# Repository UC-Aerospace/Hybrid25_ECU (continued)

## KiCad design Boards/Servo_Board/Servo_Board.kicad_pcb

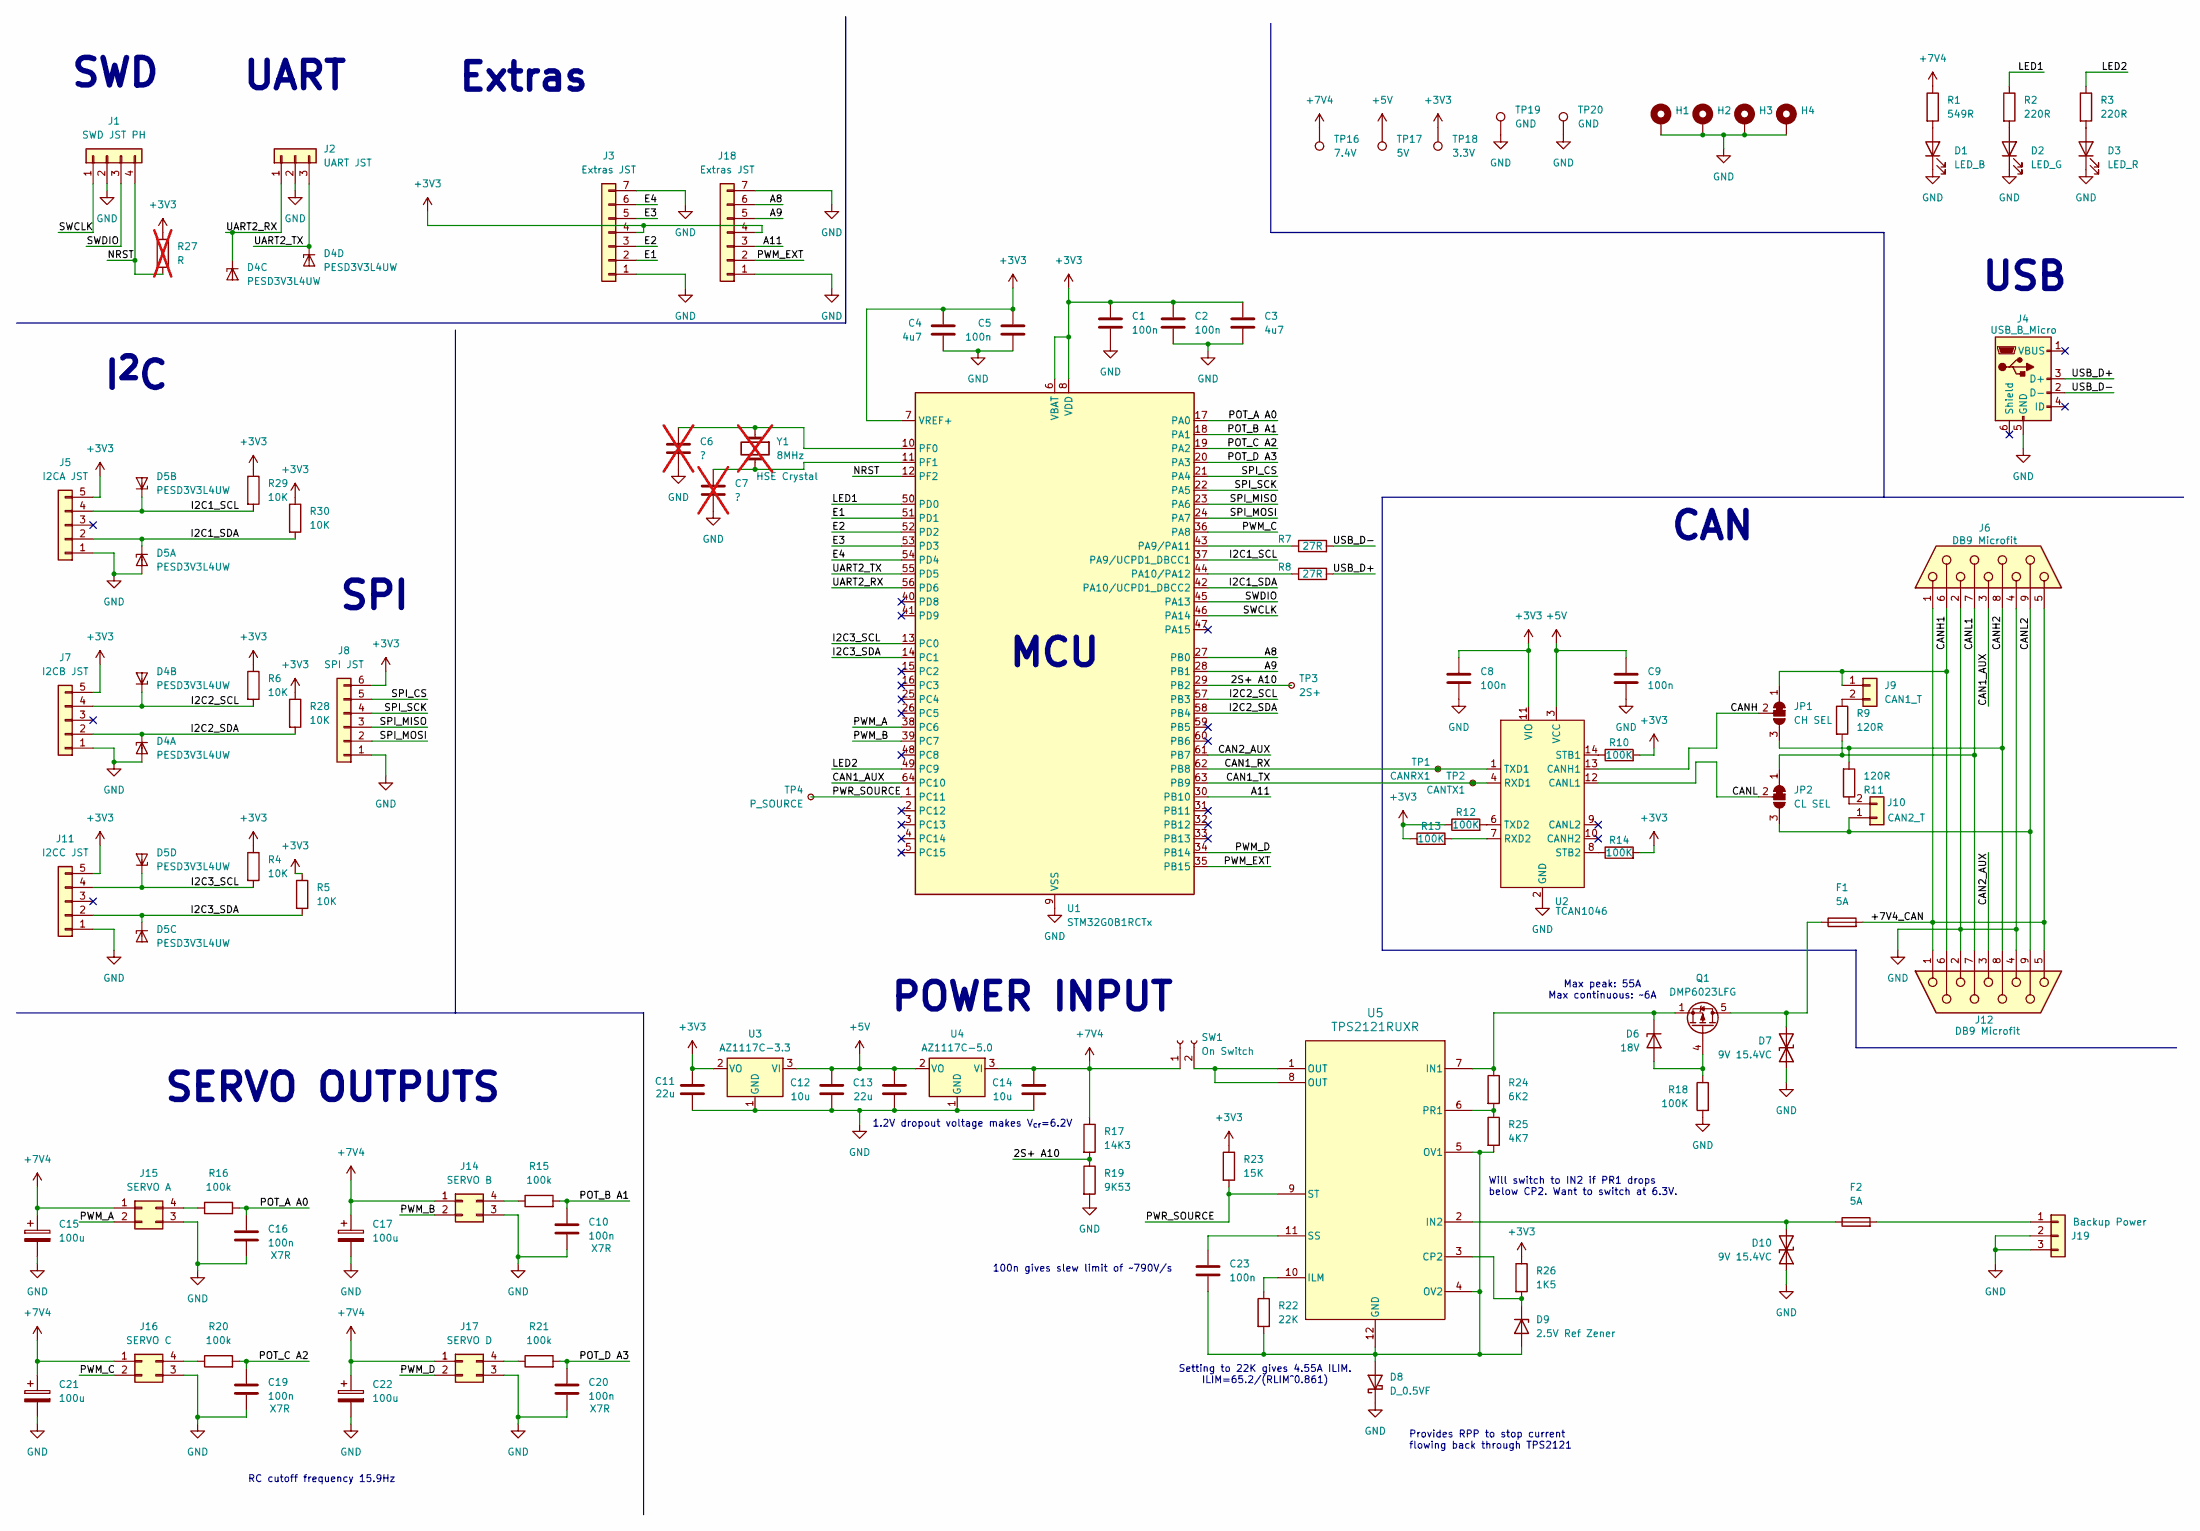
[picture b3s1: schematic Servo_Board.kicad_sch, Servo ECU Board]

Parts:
C1, C2, C5: 100n; C_0402_1005Metric
C3, C4: 4u7; C_0603_1608Metric
C6, C7: ?; C_0402_1005Metric; not fitted
C8, C9, C10, C16, C19, C20, C23: 100n; C_0603_1608Metric
C11, C13: 22u; C_1206_3216Metric
C12, C14: 10u; C_0603_1608Metric
C15, C17, C21, C22: 100u; CP_Elec_6.3x5.9; MPN SVZ1CM101E06E00RAXXX
D1: LED_B; LED_1206_3216Metric; MPN LTST-C150KRKT
D2: LED_G; LED_1206_3216Metric; MPN LTST-C150KGKT
D3: LED_R; LED_1206_3216Metric; MPN LTST-C150TBKT
D4, D5: PESD3V3L4UW; SOT-665
D6: 18V; D_SOD-323F; MPN MM3Z18VB
D7, D10: 9V 15.4VC; D_SOD-123F; MPN SMF9.0CA
D8: D_0.5VF; D_SOD-523; MPN RB521S30T5G
D9: 2.5V Ref Zener; SOT-23-3; MPN LM4040CYM3-2.5-TR
F1, F2: 5A; Fuse_1206_3216Metric
H1, H2, H3, H4: MountingHole_3.2mm_M3_DIN965_Pad_TopOnly
J1: SWD JST PH; JST_PH_B4B-PH-K_1x04_P2.00mm_Vertical; MPN B4B-PH-K-S
J2: UART JST; JST_PH_B3B-PH-K_1x03_P2.00mm_Vertical; MPN B3B-PH-K-S
J3, J18: Extras JST; JST_PH_B7B-PH-K_1x07_P2.00mm_Vertical; MPN B7B-PH-K-S
J4: USB_B_Micro; USB_Micro-B_Amphenol_10118193-0001LF_Horizontal; MPN 10118193-0001LF
J5: I2CA JST; JST_PH_B5B-PH-K_1x05_P2.00mm_Vertical; MPN B6B-PH-K-S
J6, J12: DB9 Microfit; DSUB-9_Pins_Horizontal_P2.77x2.84mm_EdgePinOffset7.70mm_Hou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; MPN 0430451027
J7: I2CB JST; JST_PH_B5B-PH-K_1x05_P2.00mm_Vertical; MPN B5B-PH-K-S
J8: SPI JST; JST_PH_B6B-PH-K_1x06_P2.00mm_Vertical
J9: CAN1_T; PinHeader_1x02_P2.54mm_Vertical
J10: CAN2_T; PinHeader_1x02_P2.54mm_Vertical
J11: I2CC JST; JST_PH_B5B-PH-K_1x05_P2.00mm_Vertical; MPN B5B-PH-K-S
J14: SERVO B; Molex_Micro-Fit_3.0_43045-0412_2x02_P3.00mm_Vertical; MPN 0430450412
J15: SERVO A; Molex_Micro-Fit_3.0_43045-0412_2x02_P3.00mm_Vertical; MPN 0430450412
J16: SERVO C; Molex_Micro-Fit_3.0_43045-0412_2x02_P3.00mm_Vertical; MPN 0430450412
J17: SERVO D; Molex_Micro-Fit_3.0_43045-0412_2x02_P3.00mm_Vertical; MPN 0430450412
J19: Backup Power; Molex_Micro-Fit_3.0_43650-0315_1x03_P3.00mm_Vertical; MPN 436500315
JP1: CH SEL; SolderJumper-3_P1.3mm_Bridged12_RoundedPad1.0x1.5mm
JP2: CL SEL; SolderJumper-3_P1.3mm_Bridged12_RoundedPad1.0x1.5mm
Q1: DMP6023LFG; Diodes_PowerDI3333-8; MPN DMP6023LFG-7
R1: 549R; R_0603_1608Metric
R2, R3: 220R; R_0603_1608Metric
R4, R5, R6, R28, R29, R30: 10K; R_0603_1608Metric
R7, R8: 27R; R_0603_1608Metric
R9, R11: 120R; R_0603_1608Metric
R10, R12, R13, R14, R18: 100K; R_0603_1608Metric
R15, R16, R20, R21: 100k; R_0603_1608Metric
R17: 14K3; R_0603_1608Metric
R19: 9K53; R_0603_1608Metric
R22: 22K; R_0603_1608Metric
R23: 15K; R_0603_1608Metric
R24: 6K2; R_0603_1608Metric
R25: 4K7; R_0603_1608Metric
R26: 1K5; R_0603_1608Metric
R27: R; R_0603_1608Metric; not fitted
SW1: On Switch; Molex_Micro-Fit_3.0_43650-0215_1x02_P3.00mm_Vertical; MPN 436500228
TP1: CANRX1; TestPoint_Pad_D1.0mm
TP2: CANTX1; TestPoint_Pad_D1.0mm
TP3: 2S+; TestPoint_Pad_D1.0mm
TP4: P_SOURCE; TestPoint_Pad_D1.0mm
TP16: 7.4V; TestPoint_Pad_D1.0mm
TP17: 5V; TestPoint_Pad_D1.0mm
TP18: 3.3V; TestPoint_Pad_D1.0mm
TP19, TP20: GND; TestPoint_Bridge_Pitch2.54mm_Drill1.3mm
U1: STM32G0B1RCTx; LQFP-64_10x10mm_P0.5mm; MPN STM32G0B1RCT6
U2: TCAN1046; SOT23_DYY_TEX; MPN TCAN1046AVDYYRQ1
U3: AZ1117C-3.3; SOT-223-3_TabPin2; MPN AZ1117CH-3.3TRG1
U4: AZ1117C-5.0; SOT-223-3_TabPin2; MPN AZ1117CH-5.0TRG1
U5: TPS2121RUXR; RUX0012A; MPN TPS2121RUXR
Y1: 8MHz; Crystal_SMD_Abracon_ABM8G-4Pin_3.2x2.5mm; not fitted

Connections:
+3V3: C1.1, C2.1, C3.1, C4.1, C5.1, C8.1, C11.1, J3.4, J5.5, J7.5, J8.6, J11.5, J18.4, R4.1, R5.1, R6.1, R10.2, R12.1, R13.1, R14.2, R23.1, R26.1, R27.2, R28.1, R29.1, R30.1, TP18.1, U1.6 (VBAT), U1.7 (VREF+), U1.8 (VDD), U2.11 (VIO), U3.2 (VO)
+5V: C9.1, C12.1, C13.1, TP17.1, U2.3 (VCC), U3.3 (VI), U4.2 (VO)
+7V4: C14.1, C15.1, C17.1, C21.1, C22.1, J14.1, J15.1, J16.1, J17.1, R1.1, R17.1, SW1.1, TP16.1, U4.3 (VI)
/2S+ A10: R17.2, R19.1, TP3.1, U1.29 (PB2)
/+7V4_CAN: F1.2, J6.1, J6.5, J12.1, J12.5
/A8: J18.6, U1.27 (PB0)
/A9: J18.5, U1.28 (PB1)
/A11: J18.3, U1.30 (PB10)
/CAN1_AUX: J6.3, U1.64 (PC10)
/CAN1_RX: TP1.1, U1.62 (PB8), U2.1 (TXD1)
/CAN1_TX: TP2.1, U1.63 (PB9), U2.4 (RXD1)
/CAN2_AUX: J12.3, U1.61 (PB7)
/CANH: JP1.2 (C), U2.13 (CANH1)
/CANH1: J6.6, J9.1, J12.6, JP1.1 (A)
/CANH2: J6.8, J12.8, JP1.3 (B), R11.2
/CANL: JP2.2 (C), U2.12 (CANL1)
/CANL1: J6.7, J12.7, JP2.1 (A), R9.2
/CANL2: J6.9, J10.1, J12.9, JP2.3 (B)
/E1: J3.2, U1.51 (PD1)
/E2: J3.3, U1.52 (PD2)
/E3: J3.5, U1.53 (PD3)
/E4: J3.6, U1.54 (PD4)
/I2C1_SCL: D5.3 (K2), J5.4, R29.2, U1.37 (PA9/UCPD1_DBCC1)
/I2C1_SDA: D5.1 (K1), J5.2, R30.2, U1.42 (PA10/UCPD1_DBCC2)
/I2C2_SCL: D4.3 (K2), J7.4, R6.2, U1.57 (PB3)
/I2C2_SDA: D4.1 (K1), J7.2, R28.2, U1.58 (PB4)
/I2C3_SCL: D5.5 (K4), J11.4, R4.2, U1.13 (PC0)
/I2C3_SDA: D5.4 (K3), J11.2, R5.2, U1.14 (PC1)
/LED1: R2.1, U1.50 (PD0)
/LED2: R3.1, U1.49 (PC9)
/NRST: J1.4, R27.1, U1.12 (PF2)
/POT_A A0: C16.1, R16.2, U1.17 (PA0)
/POT_B A1: C10.1, R15.2, U1.18 (PA1)
/POT_C A2: C19.1, R20.2, U1.19 (PA2)
/POT_D A3: C20.1, R21.2, U1.20 (PA3)
/PWM_A: J15.2, U1.38 (PC6)
/PWM_B: J14.2, U1.39 (PC7)
/PWM_C: J16.2, U1.36 (PA8)
/PWM_D: J17.2, U1.34 (PB14)
/PWM_EXT: J18.2, U1.35 (PB15)
/PWR_SOURCE: R23.2, TP4.1, U1.1 (PC11), U5.9 (ST)
/SPI_CS: J8.5, U1.21 (PA4)
/SPI_MISO: J8.3, U1.23 (PA6)
/SPI_MOSI: J8.2, U1.24 (PA7)
/SPI_SCK: J8.4, U1.22 (PA5)
/SWCLK: J1.1, U1.46 (PA14)
/SWDIO: J1.3, U1.45 (PA13)
/UART2_RX: D4.4 (K3), J2.1, U1.56 (PD6)
/UART2_TX: D4.5 (K4), J2.3, U1.55 (PD5)
/USB_D+: J4.3 (D+), R8.2
/USB_D-: J4.2 (D-), R7.2
GND: C1.2, C2.2, C3.2, C4.2, C5.2, C6.2, C7.2, C8.2, C9.2, C10.2, C11.2, C12.2, C13.2, C14.2, C15.2, C16.2, C17.2, C19.2, C20.2, C21.2, C22.2, D1.1 (K), D2.1 (K), D3.1 (K), D4.2 (A), D5.2 (A), D7.1 (A1), D8.1 (K), D10.1 (A1), H1.1, H2.1, H3.1, H4.1, J1.2, J2.2, J3.1, J3.7, J4.5 (GND), J5.1, J6.2, J6.4, J7.1, J8.1, J11.1, J12.2, J12.4, J14.3, J15.3, J16.3, J17.3, J18.1, J18.7, J19.2, J19.3, R18.2, R19.2, TP19.1, TP20.1, U1.9 (VSS), U2.2 (GND), U2.5 (GND), U3.1 (GND), U4.1 (GND)
unnamed: D1.2 (A), R1.2
unnamed: D2.2 (A), R2.2
unnamed: D3.2 (A), R3.2
unnamed: D6.2 (A), Q1.4 (G), R18.1
unnamed: D6.1 (K), Q1.1 (S), Q1.2 (S), Q1.3 (S), R24.1, U5.7 (IN1)
unnamed: D7.2 (A2), F1.1, Q1.5 (D)
unnamed: C23.2, D8.2 (A), D9.2 (A), R22.2, R25.2, U5.4 (OV2), U5.5 (OV1), U5.12 (GND)
unnamed: D9.1 (K), R26.2, U5.3 (CP2)
unnamed: D10.2 (A2), F2.1, U5.2 (IN2)
unnamed: J9.2, R9.1
unnamed: J10.2, R11.1
unnamed: J14.4, R15.1
unnamed: J15.4, R16.1
unnamed: J16.4, R20.1
unnamed: J17.4, R21.1
unnamed: F2.2, J19.1
unnamed: SW1.2, U5.1 (OUT), U5.8 (OUT)
unnamed: R7.1, U1.43 (PA9/PA11)
unnamed: R8.1, U1.44 (PA10/PA12)
unnamed: C6.1, U1.10 (PF0), Y1.1
unnamed: C7.1, U1.11 (PF1), Y1.3 (2)
unnamed: R13.2, U2.7 (RXD2)
unnamed: R10.1, U2.14 (STB1)
unnamed: R14.1, U2.8 (STB2)
unnamed: R12.2, U2.6 (TXD2)
unnamed: R22.1, U5.10 (ILM)
unnamed: R24.2, R25.1, U5.6 (PR1)
unnamed: C23.1, U5.11 (SS)

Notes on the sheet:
Extras
Max peak: 55A Max continuous: ~6A
SPI
MCU
CAN
Will switch to IN2 if PR1 drops below CP2. Want to switch at 6.3V.
RC cutoff frequency 15.9Hz
POWER INPUT
UART
I^{2}C
SERVO OUTPUTS
100n gives slew limit of ~790V/s
Setting to 22K gives 4.55A ILIM. ILIM=65.2/(RLIM^0.861)
1.2V dropout voltage makes V_{cr}=6.2V
USB
Provides RPP to stop current flowing back through TPS2121
SWD

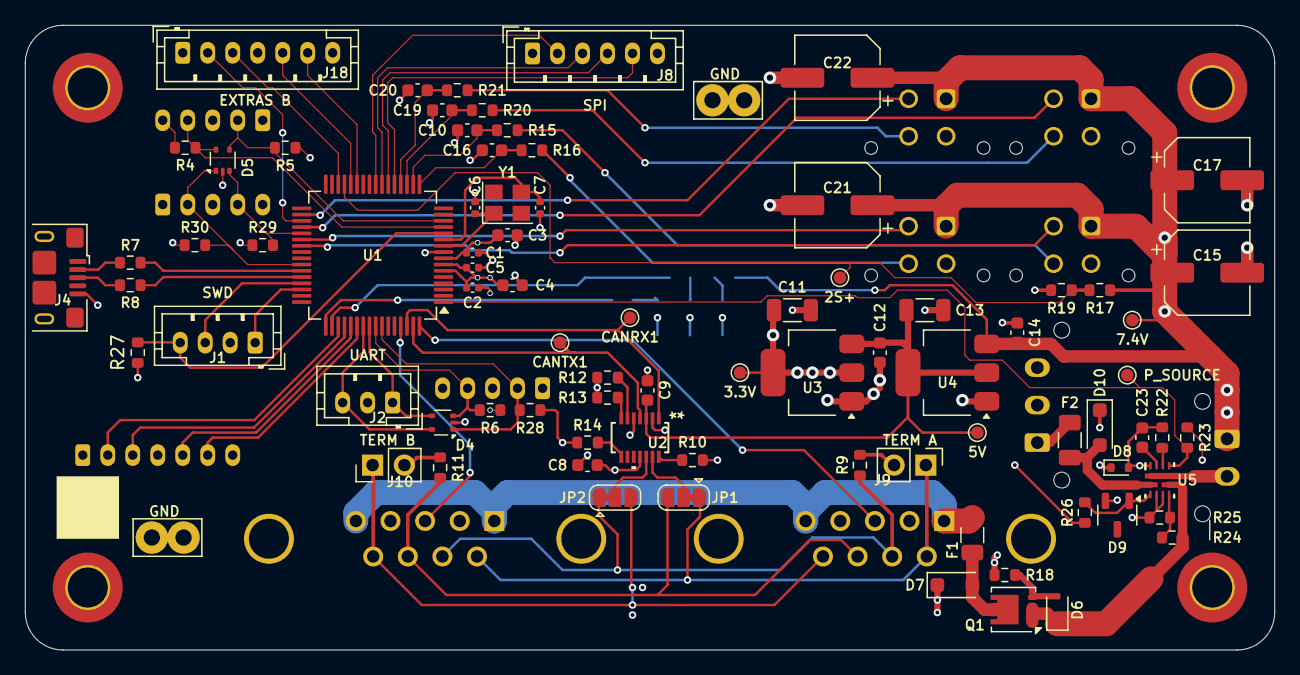
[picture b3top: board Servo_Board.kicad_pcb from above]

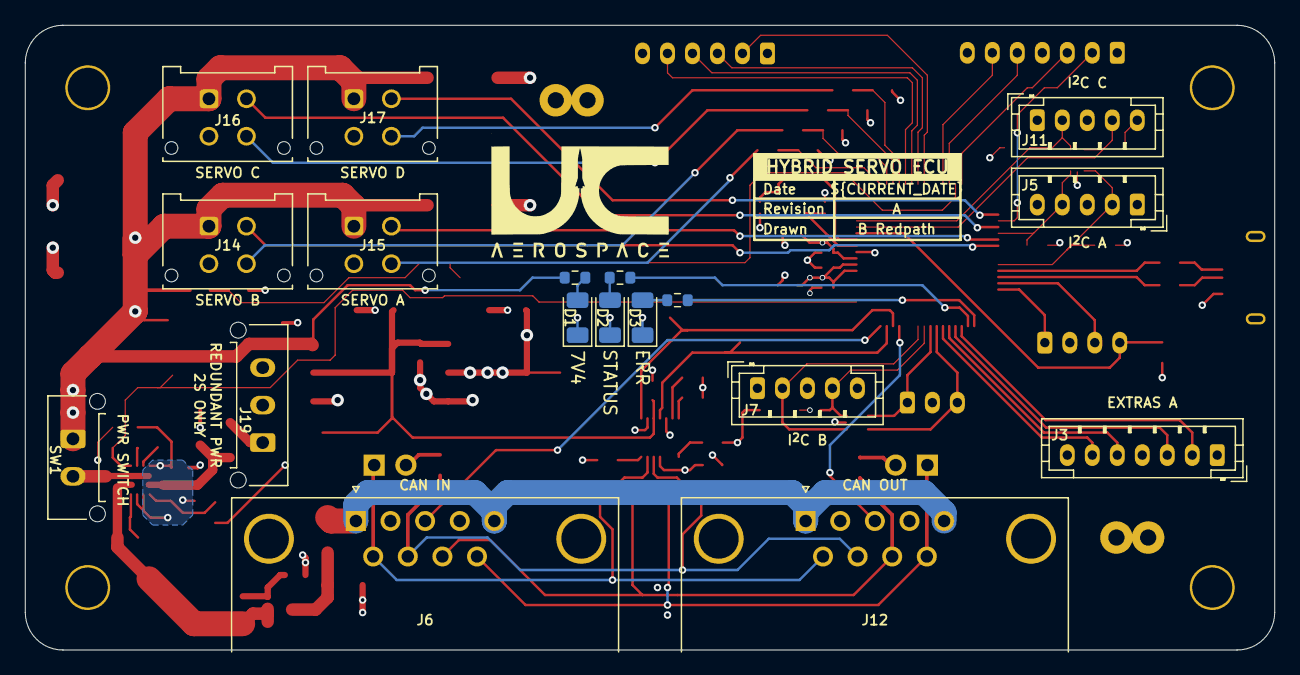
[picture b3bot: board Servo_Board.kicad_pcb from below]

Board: 4 copper layers, 100.0 x 50.0 mm, 105 parts (18 on the bottom side), 80 nets.

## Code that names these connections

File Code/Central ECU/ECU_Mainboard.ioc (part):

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Mcu.Name=STM32G0B1R(B-C-E)Tx
Mcu.Package=LQFP64
Mcu.UserName=STM32G0B1RCTx
PA0.Mode=IN0
PA0.Signal=ADC1_IN0
PA1.Mode=IN1
PA1.Signal=ADC1_IN1
PA11\ [PA9].Mode=Device
PA11\ [PA9].Signal=USB_DM
PA12\ [PA10].Mode=Device
PA12\ [PA10].Signal=USB_DP
PA13.Mode=Serial_Wire
PA13.Signal=SYS_SWDIO
PA14-BOOT0.Mode=Serial_Wire
PA14-BOOT0.Signal=SYS_SWCLK
PA2.Mode=IN2
PA2.Signal=ADC1_IN2
PA3.Mode=IN3
PA3.Signal=ADC1_IN3
PA4.GPIOParameters=GPIO_Speed,PinState,GPIO_Label
PA4.GPIO_Label=SPI1_CSS
PA4.GPIO_Speed=GPIO_SPEED_FREQ_HIGH
PA4.PinState=GPIO_PIN_SET
PA4.Signal=GPIO_Output
PA5.Mode=Full_Duplex_Master
PA5.Signal=SPI1_SCK
PA6.Mode=Full_Duplex_Master
PA6.Signal=SPI1_MISO
PA7.Mode=Full_Duplex_Master
PA7.Signal=SPI1_MOSI
PB12.GPIOParameters=GPIO_Label
PB12.GPIO_Label=CAN2_AUX
PB12.Signal=GPIO_Input
PB13.GPIOParameters=GPIO_Label
PB13.GPIO_Label=CAN1_AUX
PB13.Signal=GPIO_Input
PB14.GPIOParameters=GPIO_Label
PB14.GPIO_Label=PGOOD_HS
PB14.Signal=GPIO_Input
PB15.GPIOParameters=GPIO_Label
PB15.GPIO_Label=IMON_HS
PB15.Signal=GPIO_Input
PB3.Mode=I2C
PB3.Signal=I2C2_SCL
PB4.Mode=I2C
PB4.Signal=I2C2_SDA
PB6.GPIOParameters=GPIO_Speed
PB6.GPIO_Speed=GPIO_SPEED_FREQ_VERY_HIGH
PB6.Mode=Asynchronous
PB6.Signal=USART1_TX
PB7.GPIOParameters=GPIO_Speed,GPIO_PuPd
PB7.GPIO_PuPd=GPIO_NOPULL
PB7.GPIO_Speed=GPIO_SPEED_FREQ_VERY_HIGH
PB7.Mode=Asynchronous
PB7.Signal=USART1_RX
PB8.Mode=I2C
PB8.Signal=I2C1_SCL
PB9.Mode=I2C
PB9.Signal=I2C1_SDA
PC0.Mode=I2C
PC0.Signal=I2C3_SCL
PC1.Mode=I2C
PC1.Signal=I2C3_SDA
PC10.GPIOParameters=GPIO_Label
PC10.GPIO_Label=OX_FIRE
PC10.Signal=GPIO_Output
PC11.GPIOParameters=GPIO_Label
PC11.GPIO_Label=EMATCH2_FIRE
PC11.Signal=GPIO_Output
PC12.GPIOParameters=GPIO_Label
PC12.GPIO_Label=EMATCH1_FIRE
PC12.Signal=GPIO_Output
PC13.GPIOParameters=GPIO_Label
PC13.GPIO_Label=ARM_HS
PC13.Signal=GPIO_Output
PC14-OSC32_IN\ (PC14).Mode=LSE-External-Oscillator
PC14-OSC32_IN\ (PC14).Signal=RCC_OSC32_IN
PC15-OSC32_OUT\ (PC15).Mode=LSE-External-Oscillator
PC15-OSC32_OUT\ (PC15).Signal=RCC_OSC32_OUT
PC4.Mode=FDCAN_Activate
PC4.Signal=FDCAN1_RX
PC5.Mode=FDCAN_Activate
PC5.Signal=FDCAN1_TX
PC6.GPIOParameters=GPIO_PuPd,GPIO_Label
PC6.GPIO_Label=EMATCH2_CONT
PC6.GPIO_PuPd=GPIO_PULLUP
PC6.Signal=GPIO_Input
PC7.GPIOParameters=GPIO_PuPd,GPIO_Label
PC7.GPIO_Label=EMATCH1_CONT
PC7.GPIO_PuPd=GPIO_PULLUP
PC7.Signal=GPIO_Input
PC8.GPIOParameters=GPIO_PuPd,GPIO_Label
PC8.GPIO_Label=OX_LOWSIDE_SENSE
PC8.GPIO_PuPd=GPIO_PULLUP
PC8.Signal=GPIO_Input
PC9.GPIOParameters=GPIO_PuPd,GPIO_Label
PC9.GPIO_Label=SENSE_12V
PC9.GPIO_PuPd=GPIO_PULLUP
PC9.Signal=GPIO_Input
PD0.GPIOParameters=GPIO_Label
PD0.GPIO_Label=LED_STATUS
PD0.Signal=GPIO_Output
PD1.GPIOParameters=PinState,GPIO_PuPd,GPIO_Label,GPIO_ModeDefaultOutputPP
PD1.GPIO_Label=LED_IND_GREEN
PD1.GPIO_ModeDefaultOutputPP=GPIO_MODE_OUTPUT_OD
PD1.GPIO_PuPd=GPIO_NOPULL
PD1.PinState=GPIO_PIN_SET
PD1.Signal=GPIO_Output
PD2.GPIOParameters=PinState,GPIO_PuPd,GPIO_Label,GPIO_ModeDefaultOutputPP
PD2.GPIO_Label=LED_IND_ERROR
PD2.GPIO_ModeDefaultOutputPP=GPIO_MODE_OUTPUT_OD
PD2.GPIO_PuPd=GPIO_NOPULL
PD2.PinState=GPIO_PIN_SET
PD2.Signal=GPIO_Output
PD3.GPIOParameters=PinState,GPIO_PuPd,GPIO_Label,GPIO_ModeDefaultOutputPP
PD3.GPIO_Label=IND_HORN
PD3.GPIO_ModeDefaultOutputPP=GPIO_MODE_OUTPUT_OD
PD3.GPIO_PuPd=GPIO_NOPULL
PD3.PinState=GPIO_PIN_SET
PD3.Signal=GPIO_Output
PD4.GPIOParameters=GPIO_Label
PD4.GPIO_Label=E4
PD4.Signal=GPIO_Input
PD5.Mode=Asynchronous
PD5.Signal=USART2_TX
PD6.Mode=Asynchronous
PD6.Signal=USART2_RX
RCC.HSE_VALUE=8000000
RCC.SYSCLKFreq_VALUE=64000000
RCC.SYSCLKSource=RCC_SYSCLKSOURCE_PLLCLK
board=custom

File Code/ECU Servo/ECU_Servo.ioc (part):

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Mcu.Name=STM32G0B1R(B-C-E)Tx
Mcu.Package=LQFP64
Mcu.UserName=STM32G0B1RCTx
PA0.GPIOParameters=GPIO_Label
PA0.GPIO_Label=POT_A
PA0.Mode=IN0
PA0.Signal=ADC1_IN0
PA1.GPIOParameters=GPIO_Label
PA1.GPIO_Label=POT_B
PA1.Mode=IN1
PA1.Signal=ADC1_IN1
PA10.Mode=I2C
PA10.Signal=I2C1_SDA
PA11\ [PA9].Mode=Device
PA11\ [PA9].Signal=USB_DM
PA12\ [PA10].Mode=Device
PA12\ [PA10].Signal=USB_DP
PA13.Mode=Serial_Wire
PA13.Signal=SYS_SWDIO
PA14-BOOT0.Mode=Serial_Wire
PA14-BOOT0.Signal=SYS_SWCLK
PA2.GPIOParameters=GPIO_Label
PA2.GPIO_Label=POT_C
PA2.Mode=IN2
PA2.Signal=ADC1_IN2
PA3.GPIOParameters=GPIO_Label
PA3.GPIO_Label=POT_D
PA3.Mode=IN3
PA3.Signal=ADC1_IN3
PA4.Mode=NSS_Signal_Hard_Output
PA4.Signal=SPI1_NSS
PA5.Mode=Full_Duplex_Master
PA5.Signal=SPI1_SCK
PA6.Mode=Full_Duplex_Master
PA6.Signal=SPI1_MISO
PA7.Mode=Full_Duplex_Master
PA7.Signal=SPI1_MOSI
PA8.GPIOParameters=GPIO_Label
PA8.GPIO_Label=PWM_C
PA8.Signal=S_TIM1_CH1
PA9.Mode=I2C
PA9.Signal=I2C1_SCL
PB14.GPIOParameters=GPIO_Label
PB14.GPIO_Label=PWM_D
PB14.Signal=S_TIM15_CH1
PB2.GPIOParameters=GPIO_Label
PB2.GPIO_Label=ADC_2S
PB2.Mode=IN10
PB2.Signal=ADC1_IN10
PB3.Mode=I2C
PB3.Signal=I2C2_SCL
PB4.Mode=I2C
PB4.Signal=I2C2_SDA
PB7.GPIOParameters=GPIO_Label
PB7.GPIO_Label=CAN2_AUX
PB7.Signal=GPIO_Input
PB8.Mode=FDCAN_Activate
PB8.Signal=FDCAN1_RX
PB9.Mode=FDCAN_Activate
PB9.Signal=FDCAN1_TX
PC0.Mode=I2C
PC0.Signal=I2C3_SCL
PC1.Mode=I2C
PC1.Signal=I2C3_SDA
PC10.GPIOParameters=GPIO_Label
PC10.GPIO_Label=CAN1_AUX
PC10.Signal=GPIO_Input
PC11.GPIOParameters=GPIO_Label
PC11.GPIO_Label=PWR_SOURCE
PC11.Signal=GPIO_Input
PC6.GPIOParameters=GPIO_Label
PC6.GPIO_Label=PWM_A
PC6.Signal=S_TIM3_CH1
PC7.GPIOParameters=GPIO_Label
PC7.GPIO_Label=PWM_B
PC7.Signal=S_TIM3_CH2
PC9.GPIOParameters=GPIO_Label
PC9.GPIO_Label=LED_ERROR
PC9.Signal=GPIO_Output
PD0.GPIOParameters=GPIO_Label
PD0.GPIO_Label=LED_STATUS
PD0.Signal=GPIO_Output
PD1.GPIOParameters=PinState,GPIO_PuPd,GPIO_Label,GPIO_ModeDefaultOutputPP
PD1.GPIO_Label=Servo_A_NRST
PD1.GPIO_ModeDefaultOutputPP=GPIO_MODE_OUTPUT_OD
PD1.GPIO_PuPd=GPIO_NOPULL
PD1.PinState=GPIO_PIN_SET
PD1.Signal=GPIO_Output
PD2.GPIOParameters=PinState,GPIO_PuPd,GPIO_Label,GPIO_ModeDefaultOutputPP
PD2.GPIO_Label=Servo_B_NRST
PD2.GPIO_ModeDefaultOutputPP=GPIO_MODE_OUTPUT_OD
PD2.GPIO_PuPd=GPIO_NOPULL
PD2.PinState=GPIO_PIN_SET
PD2.Signal=GPIO_Output
PD3.GPIOParameters=PinState,GPIO_PuPd,GPIO_Label,GPIO_ModeDefaultOutputPP
PD3.GPIO_Label=Servo_C_NRST
PD3.GPIO_ModeDefaultOutputPP=GPIO_MODE_OUTPUT_OD
PD3.GPIO_PuPd=GPIO_NOPULL
PD3.PinState=GPIO_PIN_SET
PD3.Signal=GPIO_Output
PD4.GPIOParameters=PinState,GPIO_PuPd,GPIO_Label,GPIO_ModeDefaultOutputPP
PD4.GPIO_Label=Servo_D_NRST
PD4.GPIO_ModeDefaultOutputPP=GPIO_MODE_OUTPUT_OD
PD4.GPIO_PuPd=GPIO_NOPULL
PD4.PinState=GPIO_PIN_SET
PD4.Signal=GPIO_Output
PD5.Mode=Asynchronous
PD5.Signal=USART2_TX
PD6.Mode=Asynchronous
PD6.Signal=USART2_RX
PF0-OSC_IN\ (PF0).Mode=HSE-External-Oscillator
PF0-OSC_IN\ (PF0).Signal=RCC_OSC_IN
PF1-OSC_OUT\ (PF1).Mode=HSE-External-Oscillator
PF1-OSC_OUT\ (PF1).Signal=RCC_OSC_OUT
RCC.HSE_VALUE=12000000
RCC.SYSCLKFreq_VALUE=64000000
RCC.SYSCLKSource=RCC_SYSCLKSOURCE_PLLCLK
board=custom

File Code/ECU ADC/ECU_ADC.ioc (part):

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Mcu.Name=STM32G0B1R(B-C-E)Tx
Mcu.Package=LQFP64
Mcu.UserName=STM32G0B1RCTx
PA0.GPIOParameters=GPIO_Label
PA0.GPIO_Label=CJT_A0
PA0.Mode=IN0
PA0.Signal=ADC1_IN0
PA1.GPIOParameters=GPIO_Label
PA1.GPIO_Label=MIPAA_A1
PA1.Mode=IN1
PA1.Signal=ADC1_IN1
PA10.Mode=I2C
PA10.Signal=I2C1_SDA
PA11\ [PA9].Mode=Device
PA11\ [PA9].Signal=USB_DM
PA12\ [PA10].Mode=Device
PA12\ [PA10].Signal=USB_DP
PA13.Mode=Serial_Wire
PA13.Signal=SYS_SWDIO
PA14-BOOT0.Mode=Serial_Wire
PA14-BOOT0.Signal=SYS_SWCLK
PA2.GPIOParameters=GPIO_Label
PA2.GPIO_Label=MIPAB_A2
PA2.Mode=IN2
PA2.Signal=ADC1_IN2
PA4.GPIOParameters=PinState,GPIO_Label
PA4.GPIO_Label=SPI_CS
PA4.PinState=GPIO_PIN_SET
PA4.Signal=GPIO_Output
PA5.Mode=Full_Duplex_Master
PA5.Signal=SPI1_SCK
PA6.Mode=Full_Duplex_Master
PA6.Signal=SPI1_MISO
PA7.Mode=Full_Duplex_Master
PA7.Signal=SPI1_MOSI
PA9.Mode=I2C
PA9.Signal=I2C1_SCL
PB0.GPIOParameters=PinState,GPIO_Label
PB0.GPIO_Label=ADC_RST
PB0.PinState=GPIO_PIN_SET
PB0.Signal=GPIO_Output
PB1.GPIOParameters=GPIO_Label
PB1.GPIO_Label=REF5V_B1
PB1.Mode=IN9
PB1.Signal=ADC1_IN9
PB2.GPIOParameters=GPIO_Label
PB2.GPIO_Label=V2S_A10
PB2.Mode=IN10
PB2.Signal=ADC1_IN10
PB3.Mode=I2C
PB3.Signal=I2C2_SCL
PB4.Mode=I2C
PB4.Signal=I2C2_SDA
PB8.Mode=FDCAN_Activate
PB8.Signal=FDCAN1_RX
PB9.Mode=FDCAN_Activate
PB9.Signal=FDCAN1_TX
PC0.Mode=I2C
PC0.Signal=I2C3_SCL
PC1.Mode=I2C
PC1.Signal=I2C3_SDA
PC10.GPIOParameters=GPIO_Label
PC10.GPIO_Label=CAN1_AUX
PC10.Signal=GPIO_Input
PC4.GPIOParameters=GPIO_Label
PC4.GPIO_Label=SYNC
PC4.Signal=GPIO_Output
PC5.GPIOParameters=GPIO_Label
PC5.GPIO_Label=ADC_RDY
PC5.Signal=GPIO_Input
PC9.GPIOParameters=GPIO_Label
PC9.GPIO_Label=LED_IND_ERROR
PC9.Signal=GPIO_Output
PD0.GPIOParameters=GPIO_Label
PD0.GPIO_Label=LED_IND_STATUS
PD0.Signal=GPIO_Output
PD1.GPIOParameters=GPIO_Label
PD1.GPIO_Label=E1
PD1.Signal=GPIO_Input
PD2.GPIOParameters=GPIO_Label
PD2.GPIO_Label=E2
PD2.Signal=GPIO_Input
PD3.GPIOParameters=GPIO_Label
PD3.GPIO_Label=E3
PD3.Signal=GPIO_Input
PD4.GPIOParameters=GPIO_Label
PD4.GPIO_Label=E4
PD4.Signal=GPIO_Input
PD5.Mode=Asynchronous
PD5.Signal=USART2_TX
PD6.Mode=Asynchronous
PD6.Signal=USART2_RX
PF0-OSC_IN\ (PF0).Mode=HSE-External-Oscillator
PF0-OSC_IN\ (PF0).Signal=RCC_OSC_IN
PF1-OSC_OUT\ (PF1).Mode=HSE-External-Oscillator
PF1-OSC_OUT\ (PF1).Signal=RCC_OSC_OUT
RCC.HSE_VALUE=12000000
RCC.SYSCLKFreq_VALUE=64000000
RCC.SYSCLKSource=RCC_SYSCLKSOURCE_PLLCLK
board=custom

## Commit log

2025-03-21 Initial Boilerplate
2025-03-21 Added git ignore and removed backups
2025-03-21 MCU + CAN
2025-03-22 Added 422 and crystal
2025-03-23 Power regulation and crystal for MCU added to servo board.
2025-03-27 More to the central mcu plus started on ignitors and valve control
2025-03-27 CAN transceiver and D-sub connector
2025-03-28 Some more minor tweaks
2025-03-30 Servo board changes:
    Replaced buck converter with LDO voltage regulator.
    Found PWM pins on u-controller and connected them to connectors with flyback diodes.
2025-03-30 D-sub output connector added to servo board
2025-03-31 Added USB and serial programmer to Servo Board. Added servo feedback lines
2025-03-31 Forgot termination resistors
2025-04-01 Added most connectors and hooking up
2025-04-01 Nearing completion
2025-04-02 For review
2025-04-02 Finished Servo board and ADC board for review tomorrow
2025-04-04 Footprints for the servo and ADC board
2025-04-06 Changed to 0603 passives and added NRST line
2025-04-12 Added environmental P+T sensor
2025-04-12 Started layout
2025-04-13 More progress on layout
2025-04-13 Finished central ECU for review
2025-04-13 Tidy up, will send to Chris
2025-04-13 Added PDF of schematic
2025-04-15 Fixed voltage divider and comparator bias
    Re feedback from Chris still need to fix regulator power dissipation. Happy with other points being non-issues at current.
2025-04-17 Central ECU to order
2025-04-17 Rendered and updated pdf plot
2025-05-05 Ongoing changes to satellite boards and test code
2025-05-07 Working test project with CDC enabled.
2025-05-12 Somewhat done servo+adc boards
2025-05-12 Fixes and footprints
    Just thermocouples todo
2025-05-12 Selected thermocouple connector, added ferrite bead
2025-05-12 Added switch to servo board
2025-05-13 Servo nearing completion and ADC 50% layed out
2025-05-14 Nearing complete layout on both boards
2025-05-15 Completed with manufacturing files
2025-06-06 Cleaning out code for firmware
2025-06-06 Prep for ADC+Servo
2025-06-06 Some intital print functions and setting up for UID locking
2025-06-10 Updated resistors on ECU, added code to read battery voltages
2025-06-10 Added some basic OLED code to test
2025-06-12 OLED working and displaying battery percentage
2025-06-12 Minor change to CAN rates
2025-06-12 AI Spaghetti!
2025-06-13 Turns out SD is problematic
2025-06-15 RTC + SD card working
2025-06-20 RS422 still an issue
2025-07-15 Start code for servo, USB not working
2025-07-15 Rev B ADC Board
    Change ADC to QFN due to order error
    Adds voltage divider to MIPA ADC lines
2025-07-19 Added servo boiler code
2025-07-19 Unsure of change
2025-07-19 Ongoing
2025-07-21 More ongoing work, fleshed out protocol
2025-07-21 Forgot to commit ioc
2025-07-21 Updates to board to refelct rework state
2025-07-22 SD benchmarking
2025-07-22 Copilot slop
2025-07-22 Bunch of fanagling to get working and speed up SD card
2025-07-22 Removed test code
2025-07-28 CAN mainly working
2025-07-28 Some PCB changes after ADC assembly
2025-07-28 Changes before branching to make servos work
2025-07-29 Working for serial printing to control servo #1 from ECU over serial
2025-07-30 Got hardware working, part way through framing
2025-07-31 Still not working but closer, does work after with a patch to the HAL
2025-07-31 Patched the HAL
2025-07-31 Boilerplate handler
2025-08-01 Changes to reflect incorrect schematic labeling
2025-08-01 Started on CAN handlers, to merge in servo branch
2025-08-03 A bunch of work on servo board CAN comms and FSM
2025-08-04 Made workish
2025-08-06 ADS now works, needs prototypes, and built in functionality just needs CAN_TX.
2025-08-06 Many changes for the ADC board, getting somewhere
2025-08-06 More slop for ADC board, getting close
2025-08-07 Good for testing load cell
2025-08-10 Changes up the wazoo
2025-08-11 Before AI hail mary
2025-08-12 AI hail mary was a flop but hey table based state machine
2025-08-15 Post RUD
2025-08-18 READ ME...or else
2025-08-22 new readme - focus src, includes
2025-08-22 Files and framework started for new implementation of FSM and sequencer
2025-08-25 All FSM machines written and build without errors. Untested so expected to not work. Extra functionality still missing
2025-08-26 Added print statements to all states machines for testing. Fixed legacy function calls in CAN and RS422.
2025-08-26 pseudo code?
2025-08-26 lookup table for NIST Type K version 0 untested
2025-08-26 DEMO NOT WORKING ARGHHHHHHHHH
2025-08-26 Sequencer V1 written. Goes through all states and actuates everything. Currently does not check anything and is on auto fire.
2025-08-27 Before pressure testing, fixed CAN clashes
2025-08-27 Added open and close functions to tidy sequencer.
2025-08-27 Some changes as I am an idiot
2025-08-28 Calibrated for new nitrogen servo
2025-08-28 Added checks to sequencer minus SD card and pressures. Mostly commented out because trying to get everything working in wind tunnel.
2025-08-28 Added checks to stop spamming the CAN during the sequencer.
2025-08-29 Changes n stuff
2025-08-29 Some testing things
2025-09-03 Code as of "cold fire" attempt 3
2025-09-16 Fixed servos, add thermocouple cjt correction, tidy on central ECU
2025-09-18 More changes
2025-09-18 Fixes to rs422
2025-09-19 working demo
2025-09-20 Self check on central ECU code
2025-09-20 Self checks on peripherals
2025-09-24 More little tweaks
2025-10-03 Changes as of post first hot fire
2025-10-09 Updated to add underpressure check
2025-10-09 Slower post fire sequence after reviewing cold flow
2025-10-21 Add initial README
2025-10-29 More work in progress changes on README
2025-10-29 Hardware README and final change to ADC code
2025-10-29 More README changes
2025-10-29 Central ECU README
